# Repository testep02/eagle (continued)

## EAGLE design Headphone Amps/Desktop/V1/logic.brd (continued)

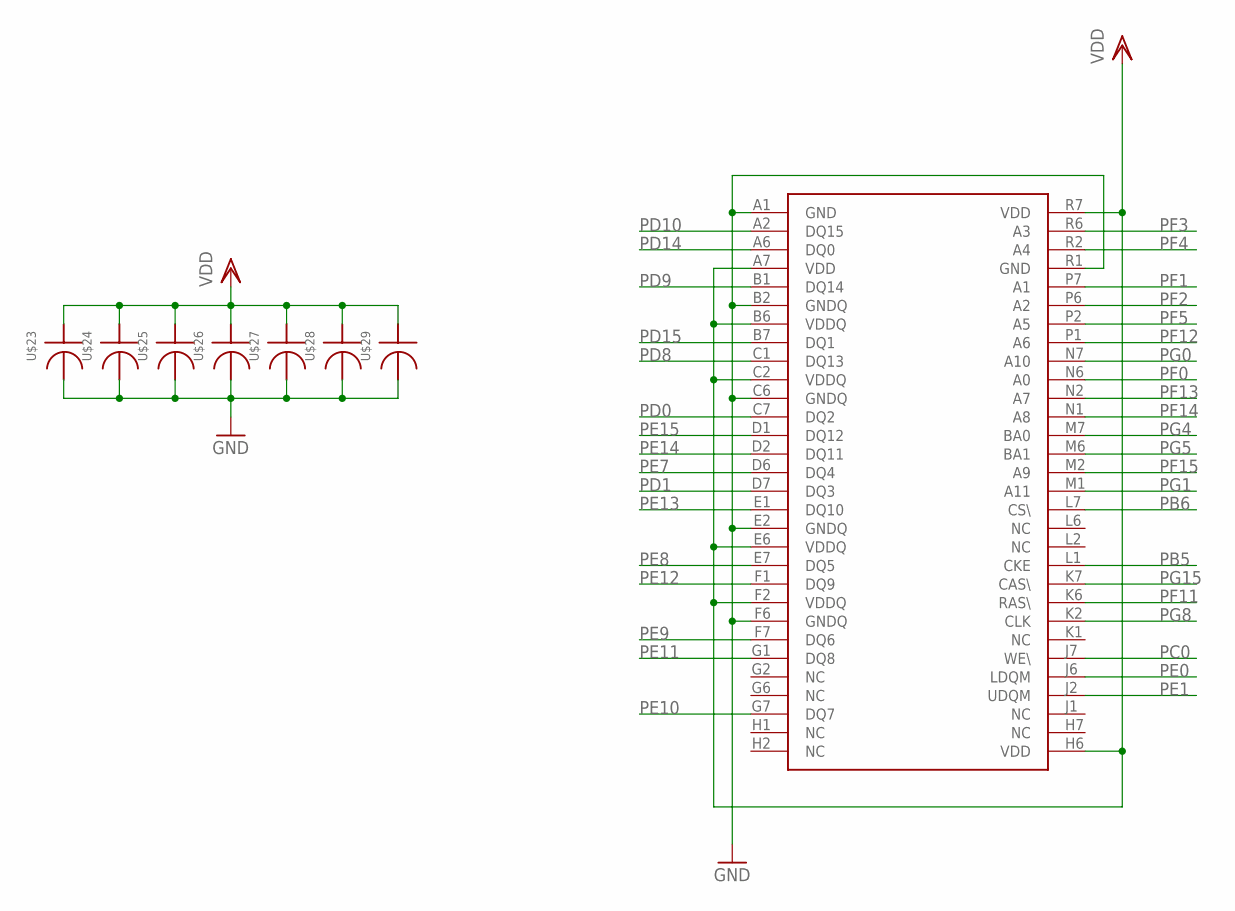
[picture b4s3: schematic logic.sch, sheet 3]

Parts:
U$2: IS42S16400J-BGA60; BGA-60
U$23, U$24, U$25, U$26, U$27, U$28, U$29: PCAP0402LEVEL3; R0402

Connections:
GND: U$2.A1 (GND), U$2.B2 (GNDQ), U$2.C6 (GNDQ), U$2.E2 (GNDQ), U$2.F6 (GNDQ), U$2.R1 (GND), U$23.P$1, U$24.P$1, U$25.P$1, U$26.P$1, U$27.P$1, U$28.P$1, U$29.P$1; also elsewhere on the board
PB5: U$2.L1 (CKE); also elsewhere on the board
PB6: U$2.L7 (CS\); also elsewhere on the board
PC0: U$2.J7 (WE\); also elsewhere on the board
PD0: U$2.C7 (DQ2); also elsewhere on the board
PD1: U$2.D7 (DQ3); also elsewhere on the board
PD8: U$2.C1 (DQ13); also elsewhere on the board
PD9: U$2.B1 (DQ14); also elsewhere on the board
PD10: U$2.A2 (DQ15); also elsewhere on the board
PD14: U$2.A6 (DQ0); also elsewhere on the board
PD15: U$2.B7 (DQ1); also elsewhere on the board
PE0: U$2.J6 (LDQM); also elsewhere on the board
PE1: U$2.J2 (UDQM); also elsewhere on the board
PE7: U$2.D6 (DQ4); also elsewhere on the board
PE8: U$2.E7 (DQ5); also elsewhere on the board
PE9: U$2.F7 (DQ6); also elsewhere on the board
PE10: U$2.G7 (DQ7); also elsewhere on the board
PE11: U$2.G1 (DQ8); also elsewhere on the board
PE12: U$2.F1 (DQ9); also elsewhere on the board
PE13: U$2.E1 (DQ10); also elsewhere on the board
PE14: U$2.D2 (DQ11); also elsewhere on the board
PE15: U$2.D1 (DQ12); also elsewhere on the board
PF0: U$2.N6 (A0); also elsewhere on the board
PF1: U$2.P7 (A1); also elsewhere on the board
PF2: U$2.P6 (A2); also elsewhere on the board
PF3: U$2.R6 (A3); also elsewhere on the board
PF4: U$2.R2 (A4); also elsewhere on the board
PF5: U$2.P2 (A5); also elsewhere on the board
PF11: U$2.K6 (RAS\); also elsewhere on the board
PF12: U$2.P1 (A6); also elsewhere on the board
PF13: U$2.N2 (A7); also elsewhere on the board
PF14: U$2.N1 (A8); also elsewhere on the board
PF15: U$2.M2 (A9); also elsewhere on the board
PG0: U$2.N7 (A10); also elsewhere on the board
PG1: U$2.M1 (A11); also elsewhere on the board
PG4: U$2.M7 (BA0); also elsewhere on the board
PG5: U$2.M6 (BA1); also elsewhere on the board
PG8: U$2.K2 (CLK); also elsewhere on the board
PG15: U$2.K7 (CAS\); also elsewhere on the board
VDD: U$2.A7 (VDD), U$2.B6 (VDDQ), U$2.C2 (VDDQ), U$2.E6 (VDDQ), U$2.F2 (VDDQ), U$2.H6 (VDD), U$2.R7 (VDD), U$23.P$2, U$24.P$2, U$25.P$2, U$26.P$2, U$27.P$2, U$28.P$2, U$29.P$2; also elsewhere on the board

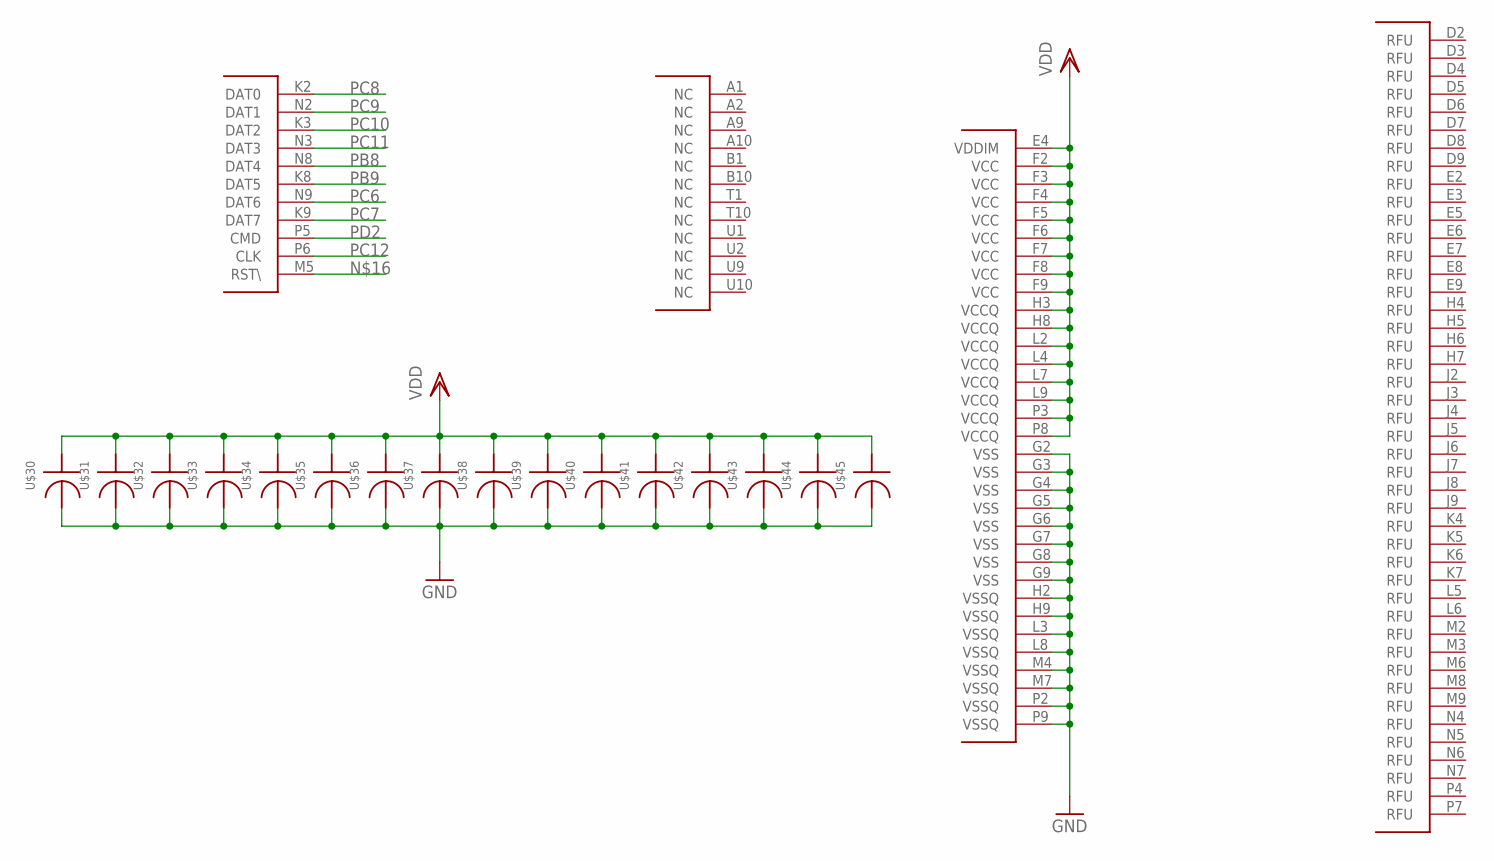
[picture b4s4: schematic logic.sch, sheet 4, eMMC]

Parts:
U$1: MTFC4GACAANA-4M; BGA-100
U$30, U$31, U$32, U$33, U$34, U$35, U$36, U$37, U$38, U$39, U$40, U$41, U$42, U$43, U$44, U$45: PCAP0402LEVEL3; R0402

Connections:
GND: U$1.G2 (VSS), U$1.G3 (VSS), U$1.G4 (VSS), U$1.G5 (VSS), U$1.G6 (VSS), U$1.G7 (VSS), U$1.G8 (VSS), U$1.G9 (VSS), U$1.H2 (VSSQ), U$1.H9 (VSSQ), U$1.L3 (VSSQ), U$1.L8 (VSSQ), U$1.M4 (VSSQ), U$1.M7 (VSSQ), U$1.P2 (VSSQ), U$1.P9 (VSSQ), U$30.P$1, U$31.P$1, U$32.P$1, U$33.P$1, U$34.P$1, U$35.P$1, U$36.P$1, U$37.P$1, U$38.P$1, U$39.P$1, U$40.P$1, U$41.P$1, U$42.P$1, U$43.P$1, U$44.P$1, U$45.P$1; also elsewhere on the board
PB8: U$1.N8 (DAT4); also elsewhere on the board
PB9: U$1.K8 (DAT5); also elsewhere on the board
PC6: U$1.N9 (DAT6); also elsewhere on the board
PC7: U$1.K9 (DAT7); also elsewhere on the board
PC8: U$1.K2 (DAT0); also elsewhere on the board
PC9: U$1.N2 (DAT1); also elsewhere on the board
PC10: U$1.K3 (DAT2); also elsewhere on the board
PC11: U$1.N3 (DAT3); also elsewhere on the board
PC12: U$1.P6 (CLK); also elsewhere on the board
PD2: U$1.P5 (CMD); also elsewhere on the board
VDD: U$1.E4 (VDDIM), U$1.F2 (VCC), U$1.F3 (VCC), U$1.F4 (VCC), U$1.F5 (VCC), U$1.F6 (VCC), U$1.F7 (VCC), U$1.F8 (VCC), U$1.F9 (VCC), U$1.H3 (VCCQ), U$1.H8 (VCCQ), U$1.L2 (VCCQ), U$1.L4 (VCCQ), U$1.L7 (VCCQ), U$1.L9 (VCCQ), U$1.P3 (VCCQ), U$1.P8 (VCCQ), U$30.P$2, U$31.P$2, U$32.P$2, U$33.P$2, U$34.P$2, U$35.P$2, U$36.P$2, U$37.P$2, U$38.P$2, U$39.P$2, U$40.P$2, U$41.P$2, U$42.P$2, U$43.P$2, U$44.P$2, U$45.P$2; also elsewhere on the board

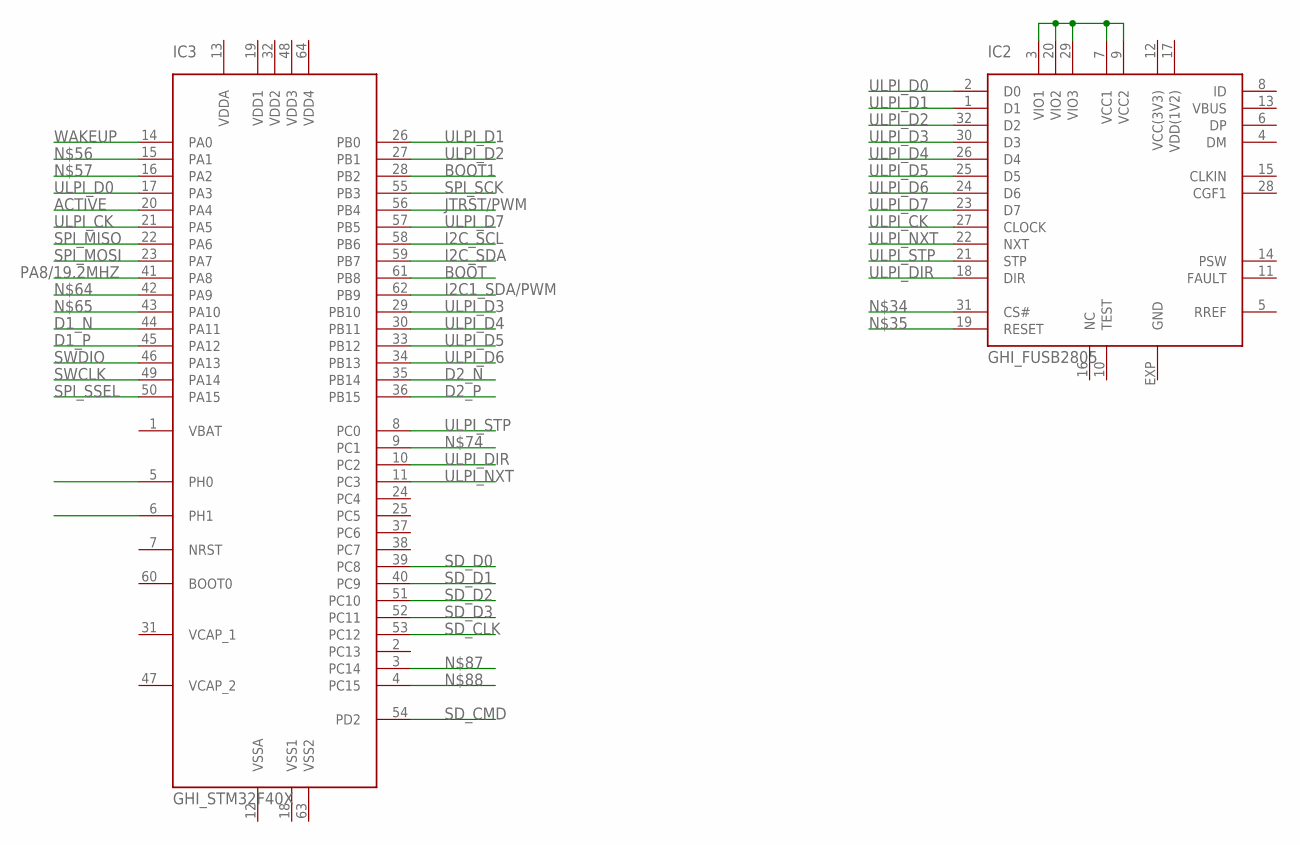
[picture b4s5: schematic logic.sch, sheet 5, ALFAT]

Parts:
IC2: GHI_FUSB2805; GHI_MLP32
IC3: GHI_STM32F40X; GHI_LQFP64

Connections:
ACTIVE: IC3.20 (PA4)
BOOT: IC3.61 (PB8)
BOOT1: IC3.28 (PB2)
D1_N: IC3.44 (PA11)
D1_P: IC3.45 (PA12)
D2_N: IC3.35 (PB14)
D2_P: IC3.36 (PB15)
I2C1_SDA/PWM: IC3.62 (PB9)
I2C_SCL: IC3.58 (PB6)
I2C_SDA: IC3.59 (PB7)
JTRST/PWM: IC3.56 (PB4)
unnamed: IC2.3 (VIO1), IC2.7 (VCC1), IC2.9 (VCC2), IC2.20 (VIO2), IC2.29 (VIO3)
PA8/19.2MHZ: IC3.41 (PA8)
SD_CLK: IC3.53 (PC12)
SD_CMD: IC3.54 (PD2)
SD_D0: IC3.39 (PC8)
SD_D1: IC3.40 (PC9)
SD_D2: IC3.51 (PC10)
SD_D3: IC3.52 (PC11)
SPI_MISO: IC3.22 (PA6)
SPI_MOSI: IC3.23 (PA7)
SPI_SCK: IC3.55 (PB3)
SPI_SSEL: IC3.50 (PA15)
SWCLK: IC3.49 (PA14)
SWDIO: IC3.46 (PA13)
ULPI_CK: IC2.27 (CLOCK), IC3.21 (PA5)
ULPI_D0: IC2.2 (D0), IC3.17 (PA3)
ULPI_D1: IC2.1 (D1), IC3.26 (PB0)
ULPI_D2: IC2.32 (D2), IC3.27 (PB1)
ULPI_D3: IC2.30 (D3), IC3.29 (PB10)
ULPI_D4: IC2.26 (D4), IC3.30 (PB11)
ULPI_D5: IC2.25 (D5), IC3.33 (PB12)
ULPI_D6: IC2.24 (D6), IC3.34 (PB13)
ULPI_D7: IC2.23 (D7), IC3.57 (PB5)
ULPI_DIR: IC2.18 (DIR), IC3.10 (PC2)
ULPI_NXT: IC2.22 (NXT), IC3.11 (PC3)
ULPI_STP: IC2.21 (STP), IC3.8 (PC0)
WAKEUP: IC3.14 (PA0)

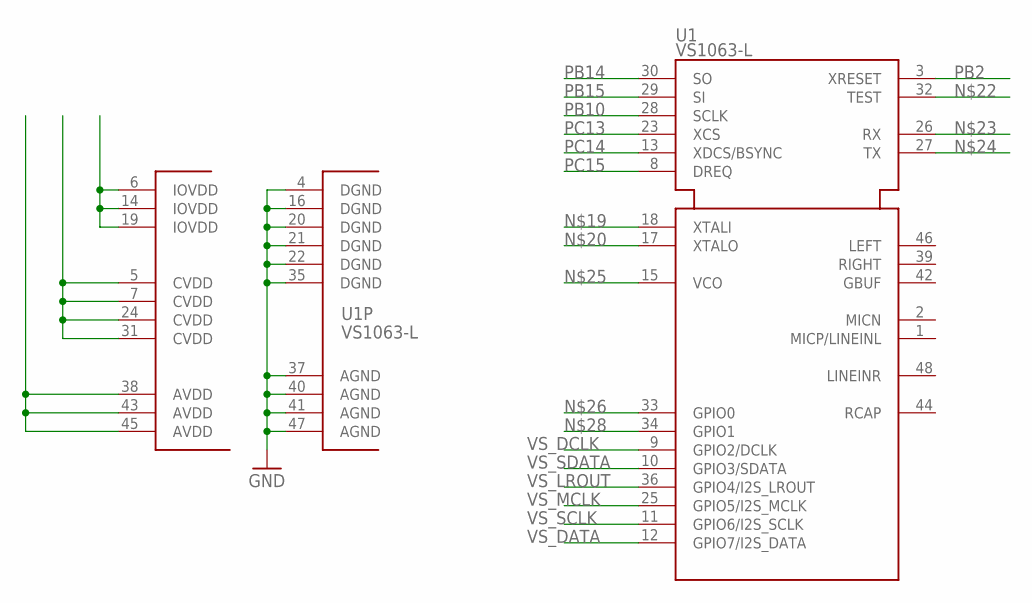
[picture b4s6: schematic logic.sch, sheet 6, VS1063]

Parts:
U1: VS1063-L; LQFP48

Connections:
GND: U1.4 (DGND), U1.16 (DGND), U1.20 (DGND), U1.21 (DGND), U1.22 (DGND), U1.35 (DGND), U1.37 (AGND), U1.40 (AGND), U1.41 (AGND), U1.47 (AGND); also elsewhere on the board
unnamed: U1.6 (IOVDD), U1.14 (IOVDD), U1.19 (IOVDD)
unnamed: U1.5 (CVDD), U1.7 (CVDD), U1.24 (CVDD), U1.31 (CVDD)
unnamed: U1.38 (AVDD), U1.43 (AVDD), U1.45 (AVDD)
PB2: U1.3 (XRESET); also elsewhere on the board
PB10: U1.28 (SCLK); also elsewhere on the board
PB14: U1.30 (SO); also elsewhere on the board
PB15: U1.29 (SI); also elsewhere on the board
PC13: U1.23 (XCS); also elsewhere on the board
PC14: U1.13 (XDCS/BSYNC); also elsewhere on the board
PC15: U1.8 (DREQ); also elsewhere on the board
VS_DATA: U1.12 (GPIO7/I2S_DATA)
VS_DCLK: U1.9 (GPIO2/DCLK)
VS_LROUT: U1.36 (GPIO4/I2S_LROUT)
VS_MCLK: U1.25 (GPIO5/I2S_MCLK)
VS_SCLK: U1.11 (GPIO6/I2S_SCLK)
VS_SDATA: U1.10 (GPIO3/SDATA)

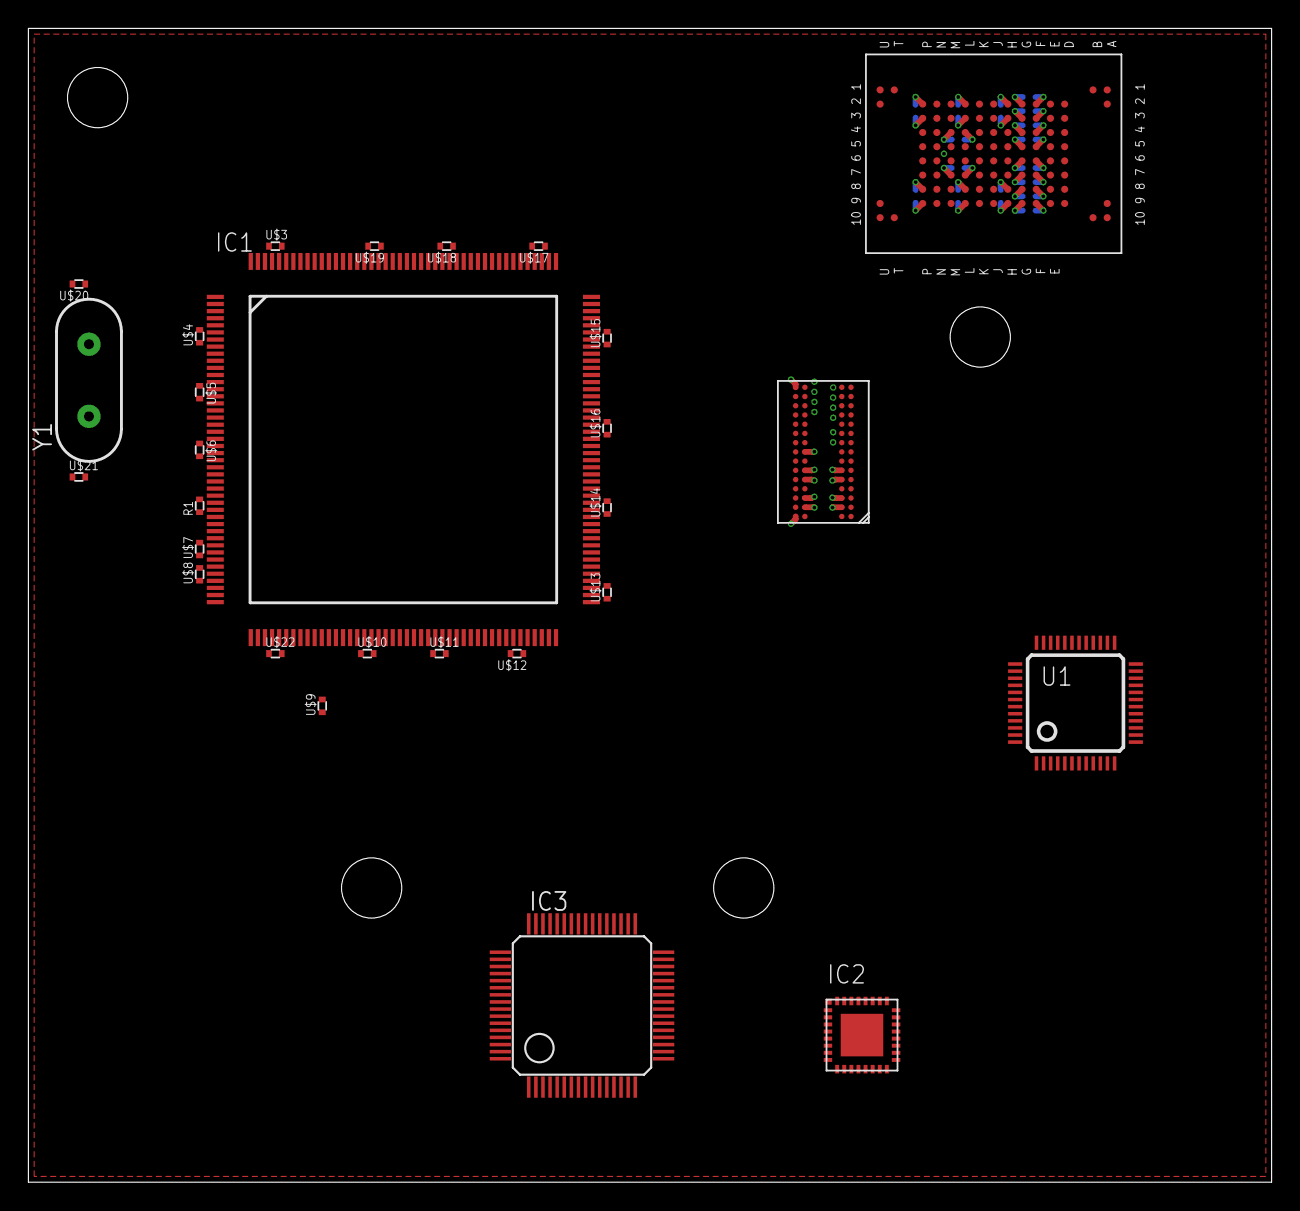
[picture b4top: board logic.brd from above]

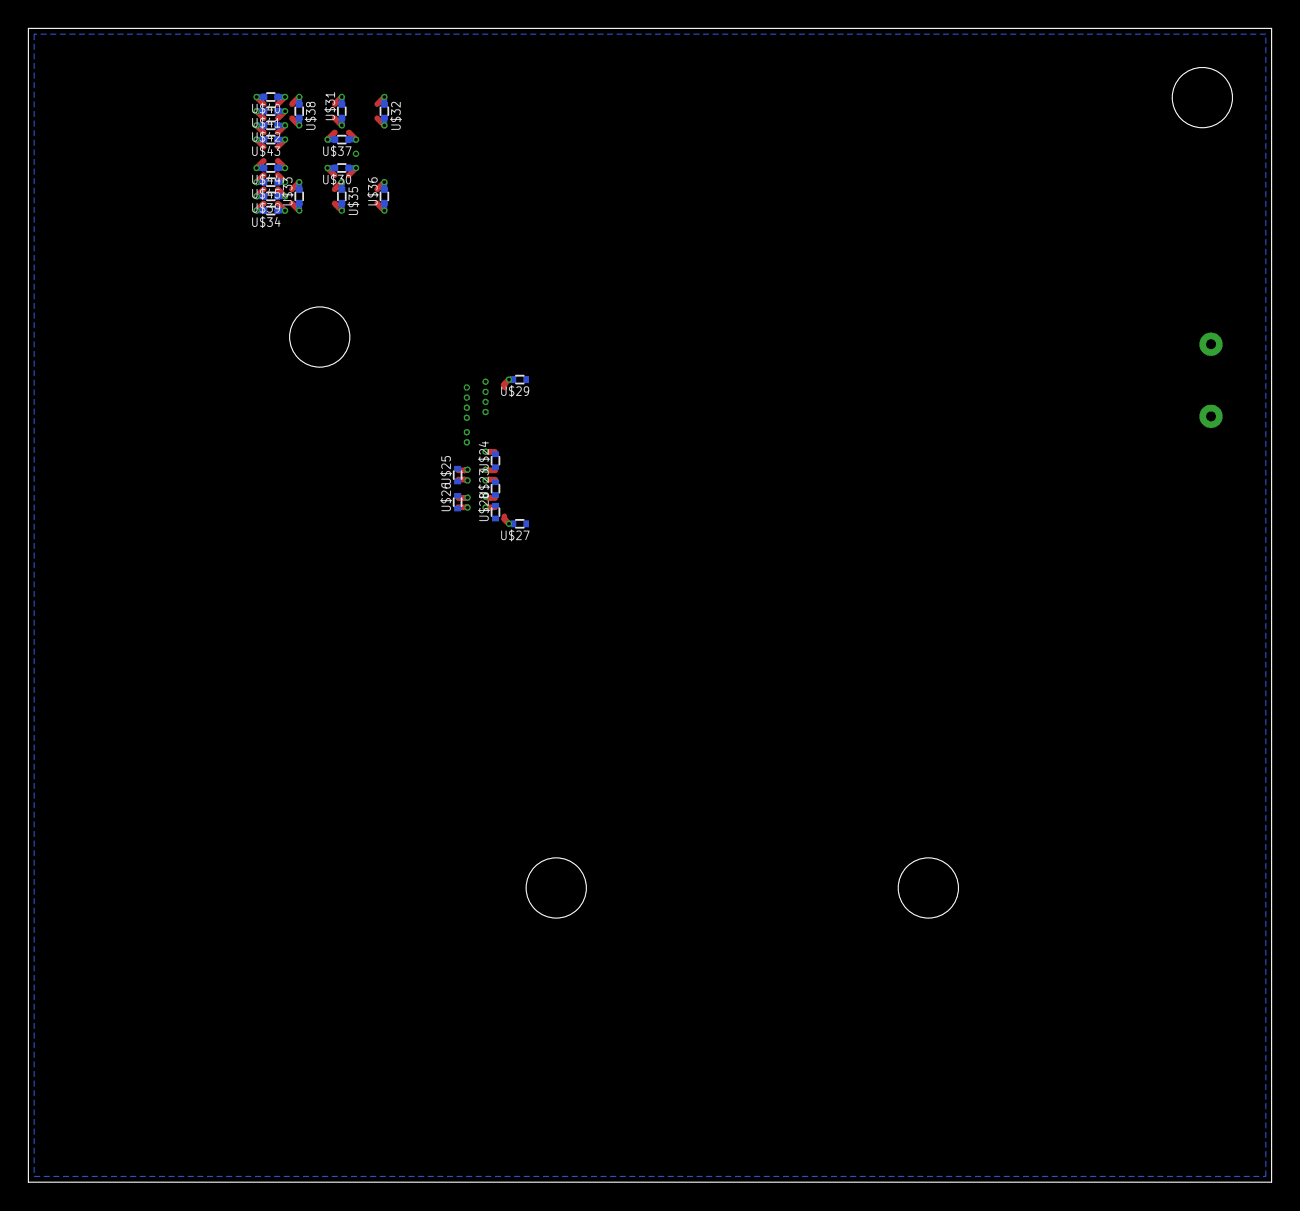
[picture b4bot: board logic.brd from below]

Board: 4 copper layers, 87.6 x 81.3 mm, 51 parts (23 on the bottom side), 76 nets.

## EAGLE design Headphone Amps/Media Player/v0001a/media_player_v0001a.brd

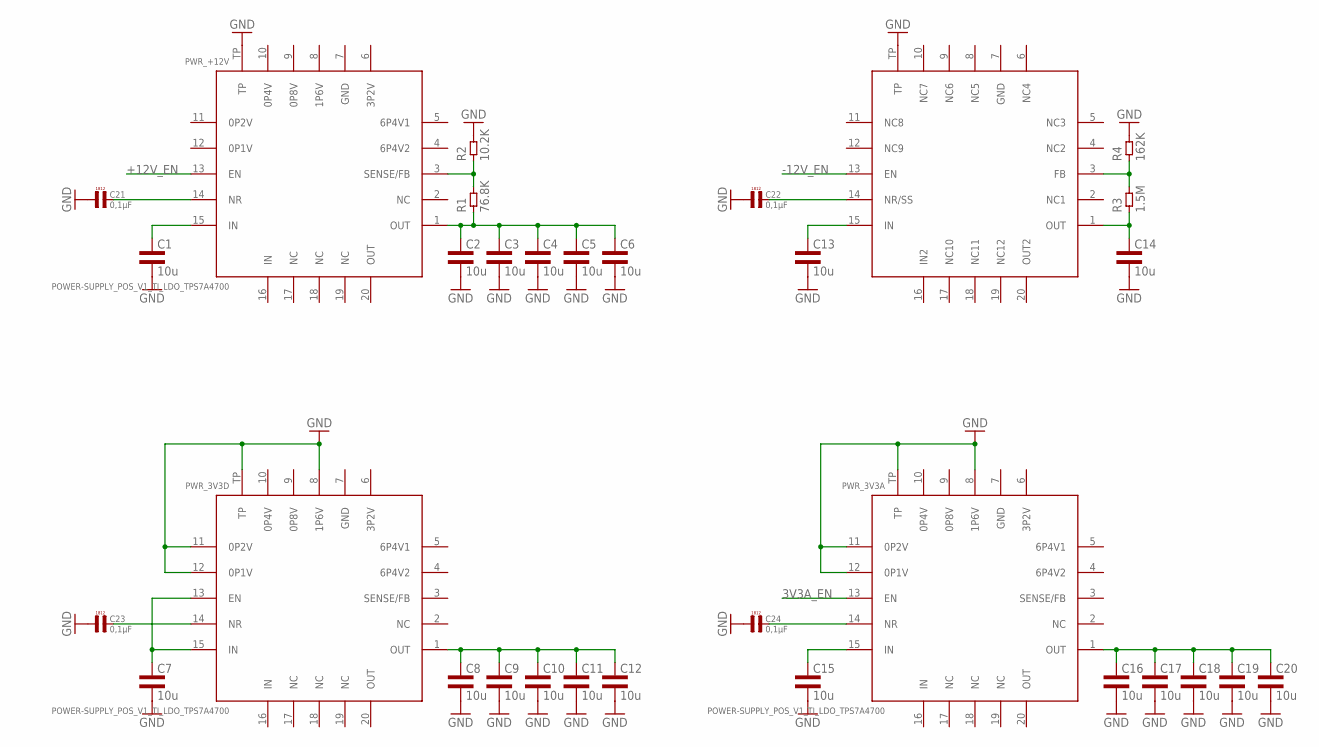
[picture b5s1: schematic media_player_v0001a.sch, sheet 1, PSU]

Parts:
C1, C2, C3, C4, C5, C6, C7, C8, C9, C10, C11, C12, C13, C14, C15, C16, C17, C18, C19, C20: 10u; 0805L3
C21, C22, C23, C24: 0,1µF; L4,8
PWR_3V3A, PWR_3V3D: POWER-SUPPLY_POS_V1_TI_LDO_TPS7A4700; POWER-SUPPLY_POS_V1_TI_LDO_VQFN-20
PWR_+12V: POWER-SUPPLY_POS_V1_TI_LDO_TPS7A4700; POWER-SUPPLY_POS_V1_TI_LDO_VQFN-20
PWR_-12V: POWER-SUPPLY_POS_V1_TI_LDO_TPS7A3301RGWT; POWER-SUPPLY_POS_V1_TI_LDO_VQFN-20
R1: 76.8K; 0603L3
R2: 10.2K; 0603L3
R3: 1.5M; 0603L3
R4: 162K; 0603L3

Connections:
3V3A: C16.1, C17.1, C18.1, C19.1, C20.1, PWR_3V3A.1 (OUT); also elsewhere on the board
3V3A_EN: PWR_3V3A.13 (EN)
3V3A_NR: C24.P$2 (2), PWR_3V3A.14 (NR)
3V3D: C8.1, C9.1, C10.1, C11.1, C12.1, PWR_3V3D.1 (OUT); also elsewhere on the board
3V3D_NR: C23.P$2 (2), PWR_3V3D.14 (NR)
+12V: C2.1, C3.1, C4.1, C5.1, C6.1, PWR_+12V.1 (OUT), R1.P$1 (1)
+12V_EN: PWR_+12V.13 (EN)
+12V_NR: C21.P$2 (2), PWR_+12V.14 (NR)
+12V_SENSE: PWR_+12V.3 (SENSE/FB), R1.P$2 (2), R2.P$1 (1)
-12V: C14.1, PWR_-12V.1 (OUT), R3.P$1 (1)
-12V_EN: PWR_-12V.13 (EN)
-12V_NR: C22.P$2 (2), PWR_-12V.14 (NR/SS)
-12V_SENSE: PWR_-12V.3 (FB), R3.P$2 (2), R4.P$1 (1)
GND: C1.2, C2.2, C3.2, C4.2, C5.2, C6.2, C7.2, C8.2, C9.2, C10.2, C11.2, C12.2, C13.2, C14.2, C15.2, C16.2, C17.2, C18.2, C19.2, C20.2, C21.P$1 (1), C22.P$1 (1), C23.P$1 (1), C24.P$1 (1), PWR_3V3A.8 (1P6V), PWR_3V3A.11 (0P2V), PWR_3V3A.12 (0P1V), PWR_3V3A.TP, PWR_3V3D.8 (1P6V), PWR_3V3D.11 (0P2V), PWR_3V3D.12 (0P1V), PWR_3V3D.TP, PWR_+12V.TP, PWR_-12V.TP, R2.P$2 (2), R4.P$2 (2); also elsewhere on the board
VIN: C1.1, C7.1, C13.1, C15.1, PWR_3V3A.15 (IN), PWR_3V3D.13 (EN), PWR_3V3D.15 (IN), PWR_+12V.15 (IN), PWR_-12V.15 (IN)

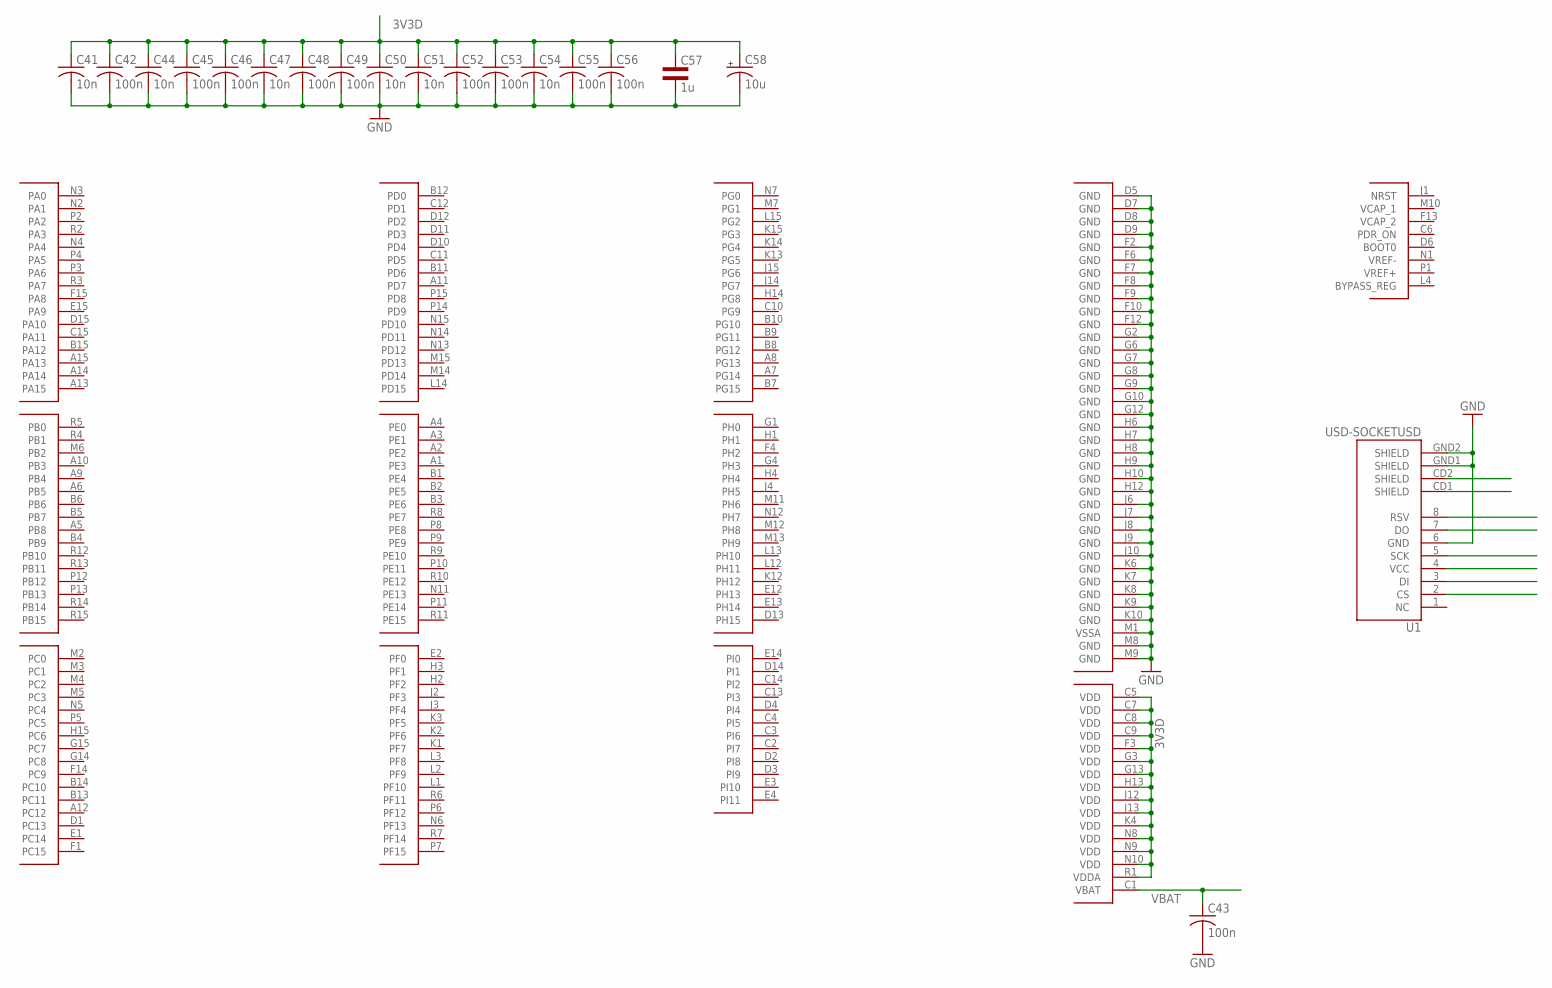
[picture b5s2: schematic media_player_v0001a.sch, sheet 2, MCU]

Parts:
C41, C44, C47, C50, C51, C54: 10n; C0201
C42, C43, C45, C46, C48, C49, C52, C53, C55, C56: 100n; C0201
C57: 1u; 0805L3
C58: 10u; A/3216-18R
U1: USD-SOCKETUSD; USD-SOCKET-PP
U$1: STM32_32BIT_MCU_STM32F407IG; STM32_32BIT_MCU_UFBGA176+25

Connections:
3V3D: C41.1, C42.1, C44.1, C45.1, C46.1, C47.1, C48.1, C49.1, C50.1, C51.1, C52.1, C53.1, C54.1, C55.1, C56.1, C57.1, C58.+, U$1.C5 (VDD), U$1.C7 (VDD), U$1.C8 (VDD), U$1.C9 (VDD), U$1.F3 (VDD), U$1.G3 (VDD), U$1.G13 (VDD), U$1.H13 (VDD), U$1.J12 (VDD), U$1.J13 (VDD), U$1.K4 (VDD), U$1.N8 (VDD), U$1.N9 (VDD), U$1.N10 (VDD), U$1.R1 (VDDA); also elsewhere on the board
GND: C41.2, C42.2, C43.2, C44.2, C45.2, C46.2, C47.2, C48.2, C49.2, C50.2, C51.2, C52.2, C53.2, C54.2, C55.2, C56.2, C57.2, C58.-, U1.6 (GND), U1.GND1 (SHIELD), U1.GND2 (SHIELD), U$1.D5 (GND), U$1.D7 (GND), U$1.D8 (GND), U$1.D9 (GND), U$1.F2 (GND), U$1.F6 (GND), U$1.F7 (GND), U$1.F8 (GND), U$1.F9 (GND), U$1.F10 (GND), U$1.F12 (GND), U$1.G2 (GND), U$1.G6 (GND), U$1.G7 (GND), U$1.G8 (GND), U$1.G9 (GND), U$1.G10 (GND), U$1.G12 (GND), U$1.H6 (GND), U$1.H7 (GND), U$1.H8 (GND), U$1.H9 (GND), U$1.H10 (GND), U$1.H12 (GND), U$1.J6 (GND), U$1.J7 (GND), U$1.J8 (GND), U$1.J9 (GND), U$1.J10 (GND), U$1.K6 (GND), U$1.K7 (GND), U$1.K8 (GND), U$1.K9 (GND), U$1.K10 (GND), U$1.M1 (VSSA), U$1.M8 (GND), U$1.M9 (GND); also elsewhere on the board
VBAT: C43.1, U$1.C1 (VBAT)

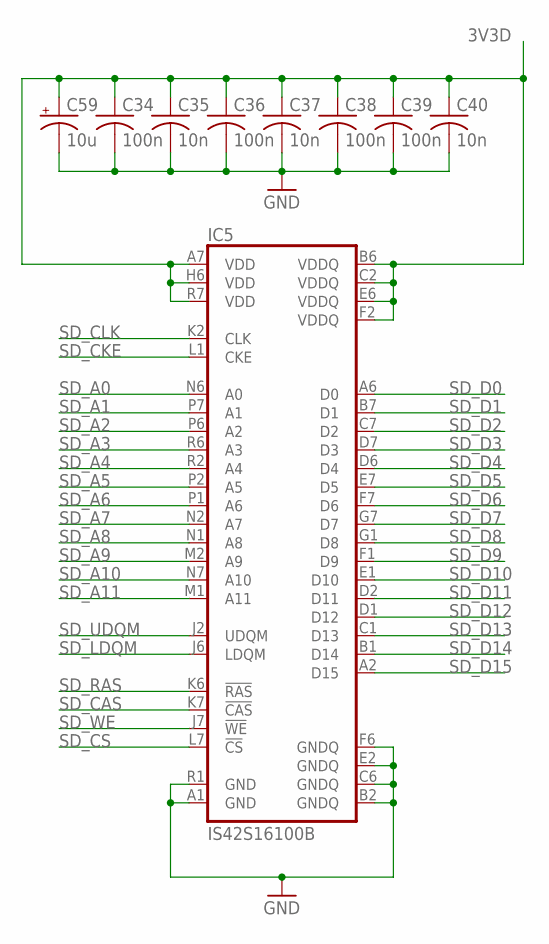
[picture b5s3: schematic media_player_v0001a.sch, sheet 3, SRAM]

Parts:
C34, C36, C38, C39: 100n; C0201
C35, C37, C40: 10n; C0201
C59: 10u; A/3216-18R
IC5: IS42S16100B; MBGA60

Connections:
3V3D: C34.1, C35.1, C36.1, C37.1, C38.1, C39.1, C40.1, C59.+, IC5.A7 (VDD), IC5.B6 (VDDQ), IC5.C2 (VDDQ), IC5.E6 (VDDQ), IC5.F2 (VDDQ), IC5.H6 (VDD), IC5.R7 (VDD); also elsewhere on the board
GND: C34.2, C35.2, C36.2, C37.2, C38.2, C39.2, C40.2, C59.-, IC5.A1 (GND), IC5.B2 (GNDQ), IC5.C6 (GNDQ), IC5.E2 (GNDQ), IC5.F6 (GNDQ), IC5.R1 (GND); also elsewhere on the board
SD_A0: IC5.N6 (A0)
SD_A1: IC5.P7 (A1)
SD_A2: IC5.P6 (A2)
SD_A3: IC5.R6 (A3)
SD_A4: IC5.R2 (A4)
SD_A5: IC5.P2 (A5)
SD_A6: IC5.P1 (A6)
SD_A7: IC5.N2 (A7)
SD_A8: IC5.N1 (A8)
SD_A9: IC5.M2 (A9)
SD_A10: IC5.N7 (A10)
SD_A11: IC5.M1 (A11)
SD_CAS: IC5.K7 (!CAS)
SD_CKE: IC5.L1 (CKE)
SD_CLK: IC5.K2 (CLK)
SD_CS: IC5.L7 (!CS)
SD_D0: IC5.A6 (D0)
SD_D1: IC5.B7 (D1)
SD_D2: IC5.C7 (D2)
SD_D3: IC5.D7 (D3)
SD_D4: IC5.D6 (D4)
SD_D5: IC5.E7 (D5)
SD_D6: IC5.F7 (D6)
SD_D7: IC5.G7 (D7)
SD_D8: IC5.G1 (D8)
SD_D9: IC5.F1 (D9)
SD_D10: IC5.E1 (D10)
SD_D11: IC5.D2 (D11)
SD_D12: IC5.D1 (D12)
SD_D13: IC5.C1 (D13)
SD_D14: IC5.B1 (D14)
SD_D15: IC5.A2 (D15)
SD_LDQM: IC5.J6 (LDQM)
SD_RAS: IC5.K6 (!RAS)
SD_UDQM: IC5.J2 (UDQM)
SD_WE: IC5.J7 (!WE)

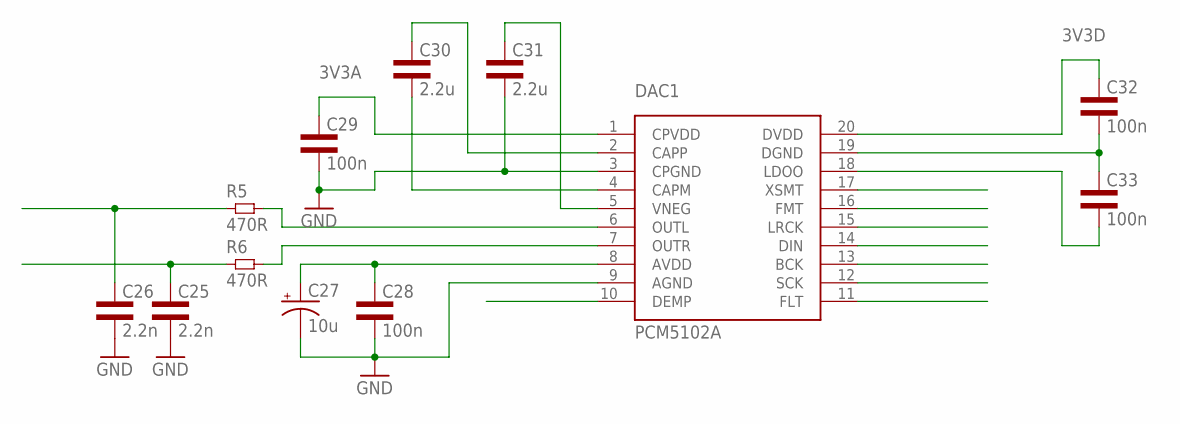
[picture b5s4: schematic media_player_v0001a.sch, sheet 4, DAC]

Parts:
C25, C26: 2.2n; 0805L3
C27: 10u; A/3216-18R
C28, C29, C32, C33: 100n; 0603L3
C30, C31: 2.2u; 0805L3
DAC1: PCM5102A; R-PDSO-G20_65
R5, R6: 470R; 0805L3

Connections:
3V3A: C29.P$1 (1), DAC1.1 (CPVDD); also elsewhere on the board
3V3D: C32.P$1 (1), DAC1.20 (DVDD); also elsewhere on the board
GND: C25.2, C26.2, C27.-, C28.P$2 (2), C29.P$2 (2), C31.2, DAC1.3 (CPGND), DAC1.9 (AGND); also elsewhere on the board
unnamed: C25.1, R6.1
unnamed: C26.1, R5.1
unnamed: DAC1.6 (OUTL), R5.2
unnamed: DAC1.7 (OUTR), R6.2
unnamed: C27.+, C28.P$1 (1), DAC1.8 (AVDD)
unnamed: C30.2, DAC1.4 (CAPM)
unnamed: C30.1, DAC1.2 (CAPP)
unnamed: C31.1, DAC1.5 (VNEG)
unnamed: C32.P$2 (2), C33.P$1 (1), DAC1.19 (DGND)
unnamed: C33.P$2 (2), DAC1.18 (LDOO)

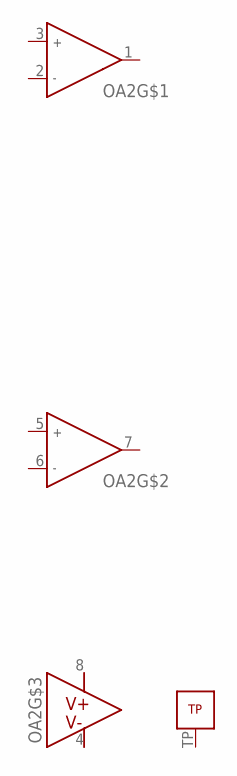
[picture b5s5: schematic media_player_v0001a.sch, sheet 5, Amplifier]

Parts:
OA2: OPA1612; S-PWSON-N8

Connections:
V+: OA2.8 (V+)
V-: OA2.4 (V-)

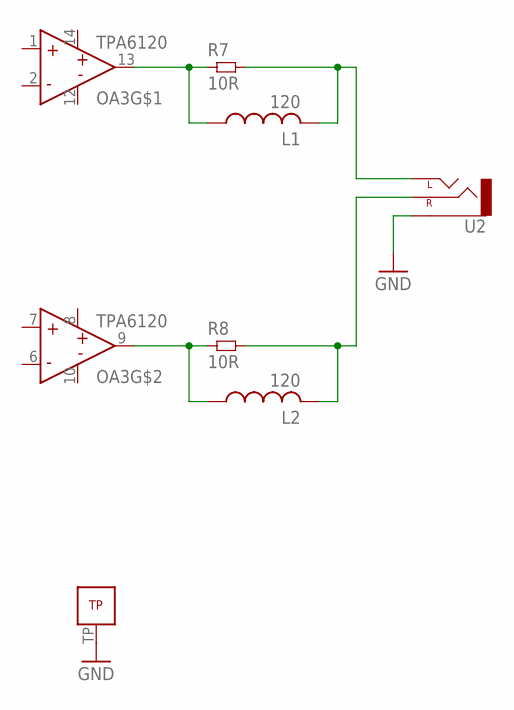
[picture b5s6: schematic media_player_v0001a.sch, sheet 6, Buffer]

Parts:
L1, L2: 120; L2012C
OA3: TPA6120QFN; S-PVQFN-N14
R7, R8: 10R; 0805L3
U2: AUDIO-JACKSMD2; AUDIO-JACK-3.5MM-SMD

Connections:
GND: OA3.TP, U2.SLEEVE; also elsewhere on the board
unnamed: L2.1, OA3.9 (OUT), R8.1
unnamed: L2.2, R8.2, U2.RING (RIGHT)
unnamed: L1.2, R7.2, U2.TIP (LEFT)
unnamed: L1.1, OA3.13 (OUT), R7.1

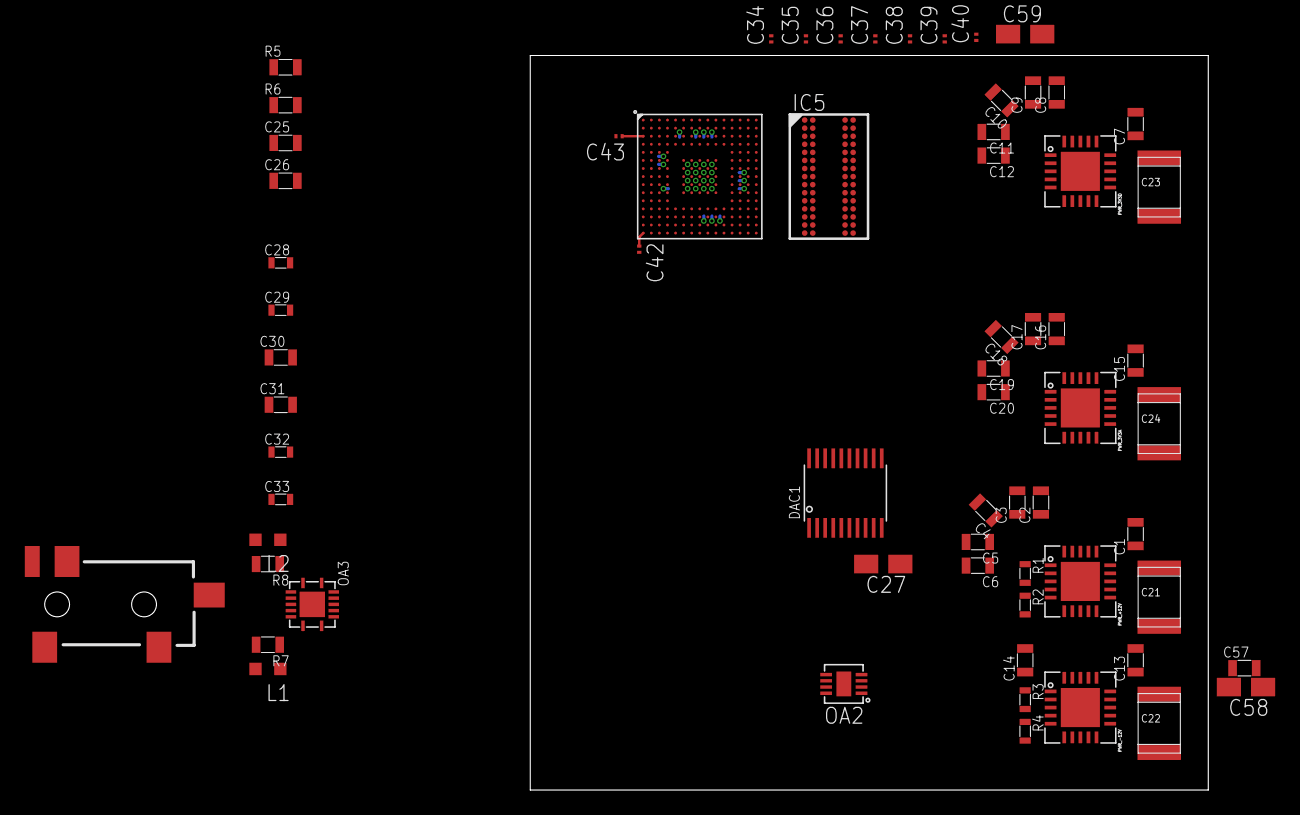
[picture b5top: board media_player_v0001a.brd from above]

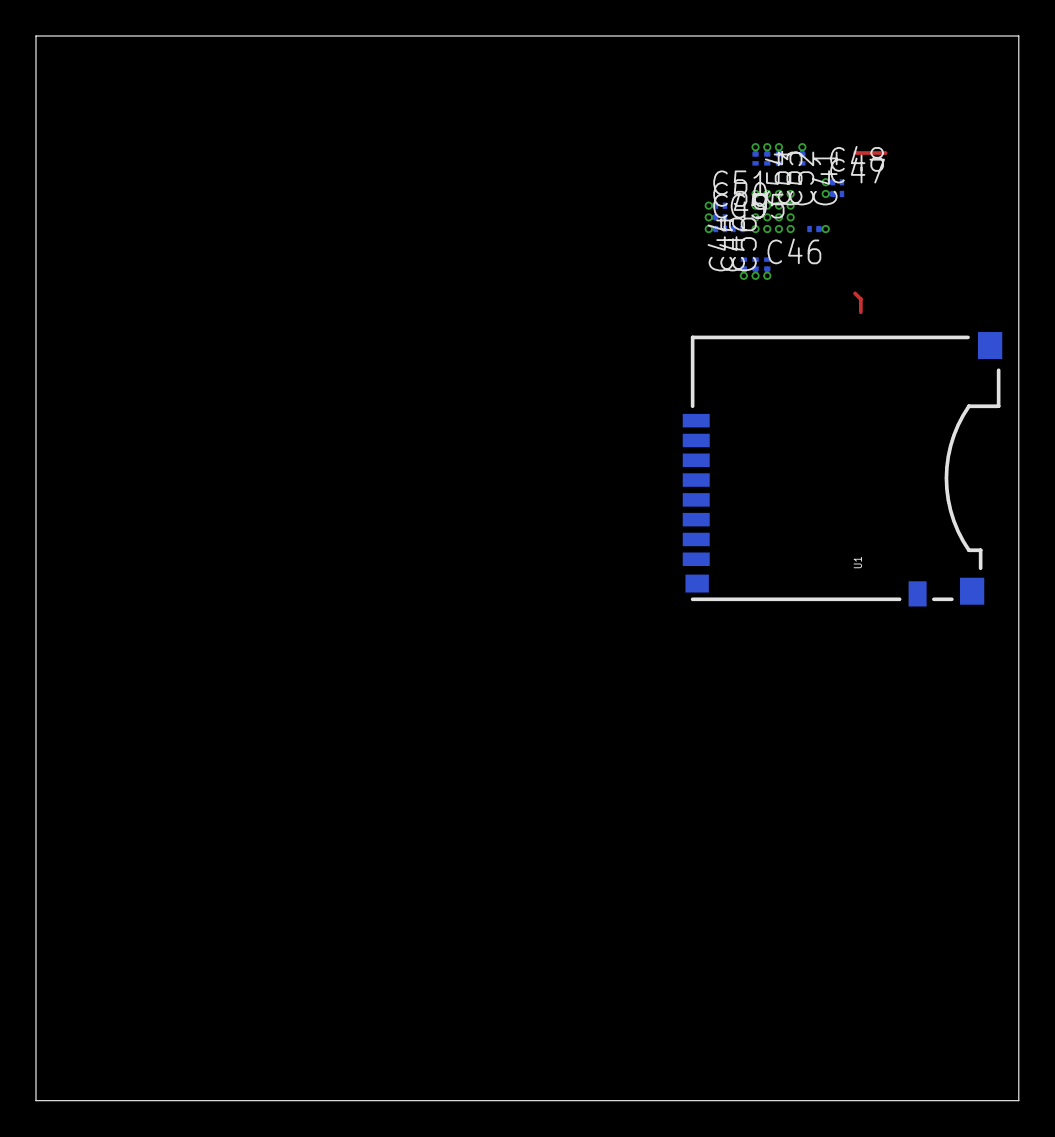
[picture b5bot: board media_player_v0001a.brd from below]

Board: 2 copper layers, 54.6 x 59.1 mm, 80 parts (15 on the bottom side), 27 nets.
